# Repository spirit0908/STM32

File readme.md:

# Presentation of the project

## Modules
- Light management (dimmer, timer, LED strips...)
- Switch management
- Security Keypad
- Heat management

## Boards
- Development board (Proto board)
- Wall switch board
- Light control board
- Heater control board

## Architecture

Distributed network based on CAN bus

```
                        temp.                   wall
  I/O  I/O              sensor          light  switch
   |    |                 |               |       |
 +-+----+-----+     +-----+------+     +--+-------+-+
 |            |     |            |     |            |
 |  Module 1  |     |  Module 3  |     |  Moduel 5  |
 |            |     |            |     |            |
 +-----+------+     +-----+------+     +-----+------+ 
       |                  |                  |
       +-----+------------+-----+------------+-------- CAN Bus
             |                  |
       +-----+------+     +-----+------+ 
       |            |     |            |
       |  Module 2  |     |  Module 4  |
       |            |     |            |
       +-+-------+--+     +-----+------+
         |       |              |
       RFID   iButton      smart meter
      reader  reader        interface
```

## Boards

### Proto board
- LCD
- 4x switch
- 4x control output (RGBW)
- RS232
- CAN

### Relay board
- 4x switch
- 4x control output (RGBW)
- 6x relay output
- RS232
- CAN

### Intercom board
- 3x sensor input
- 2x relay output
- RS232
- CAN

# How to use

## How to compile

make

## How to execute the tests

make test

Test results location: out/tests/Test_report.html

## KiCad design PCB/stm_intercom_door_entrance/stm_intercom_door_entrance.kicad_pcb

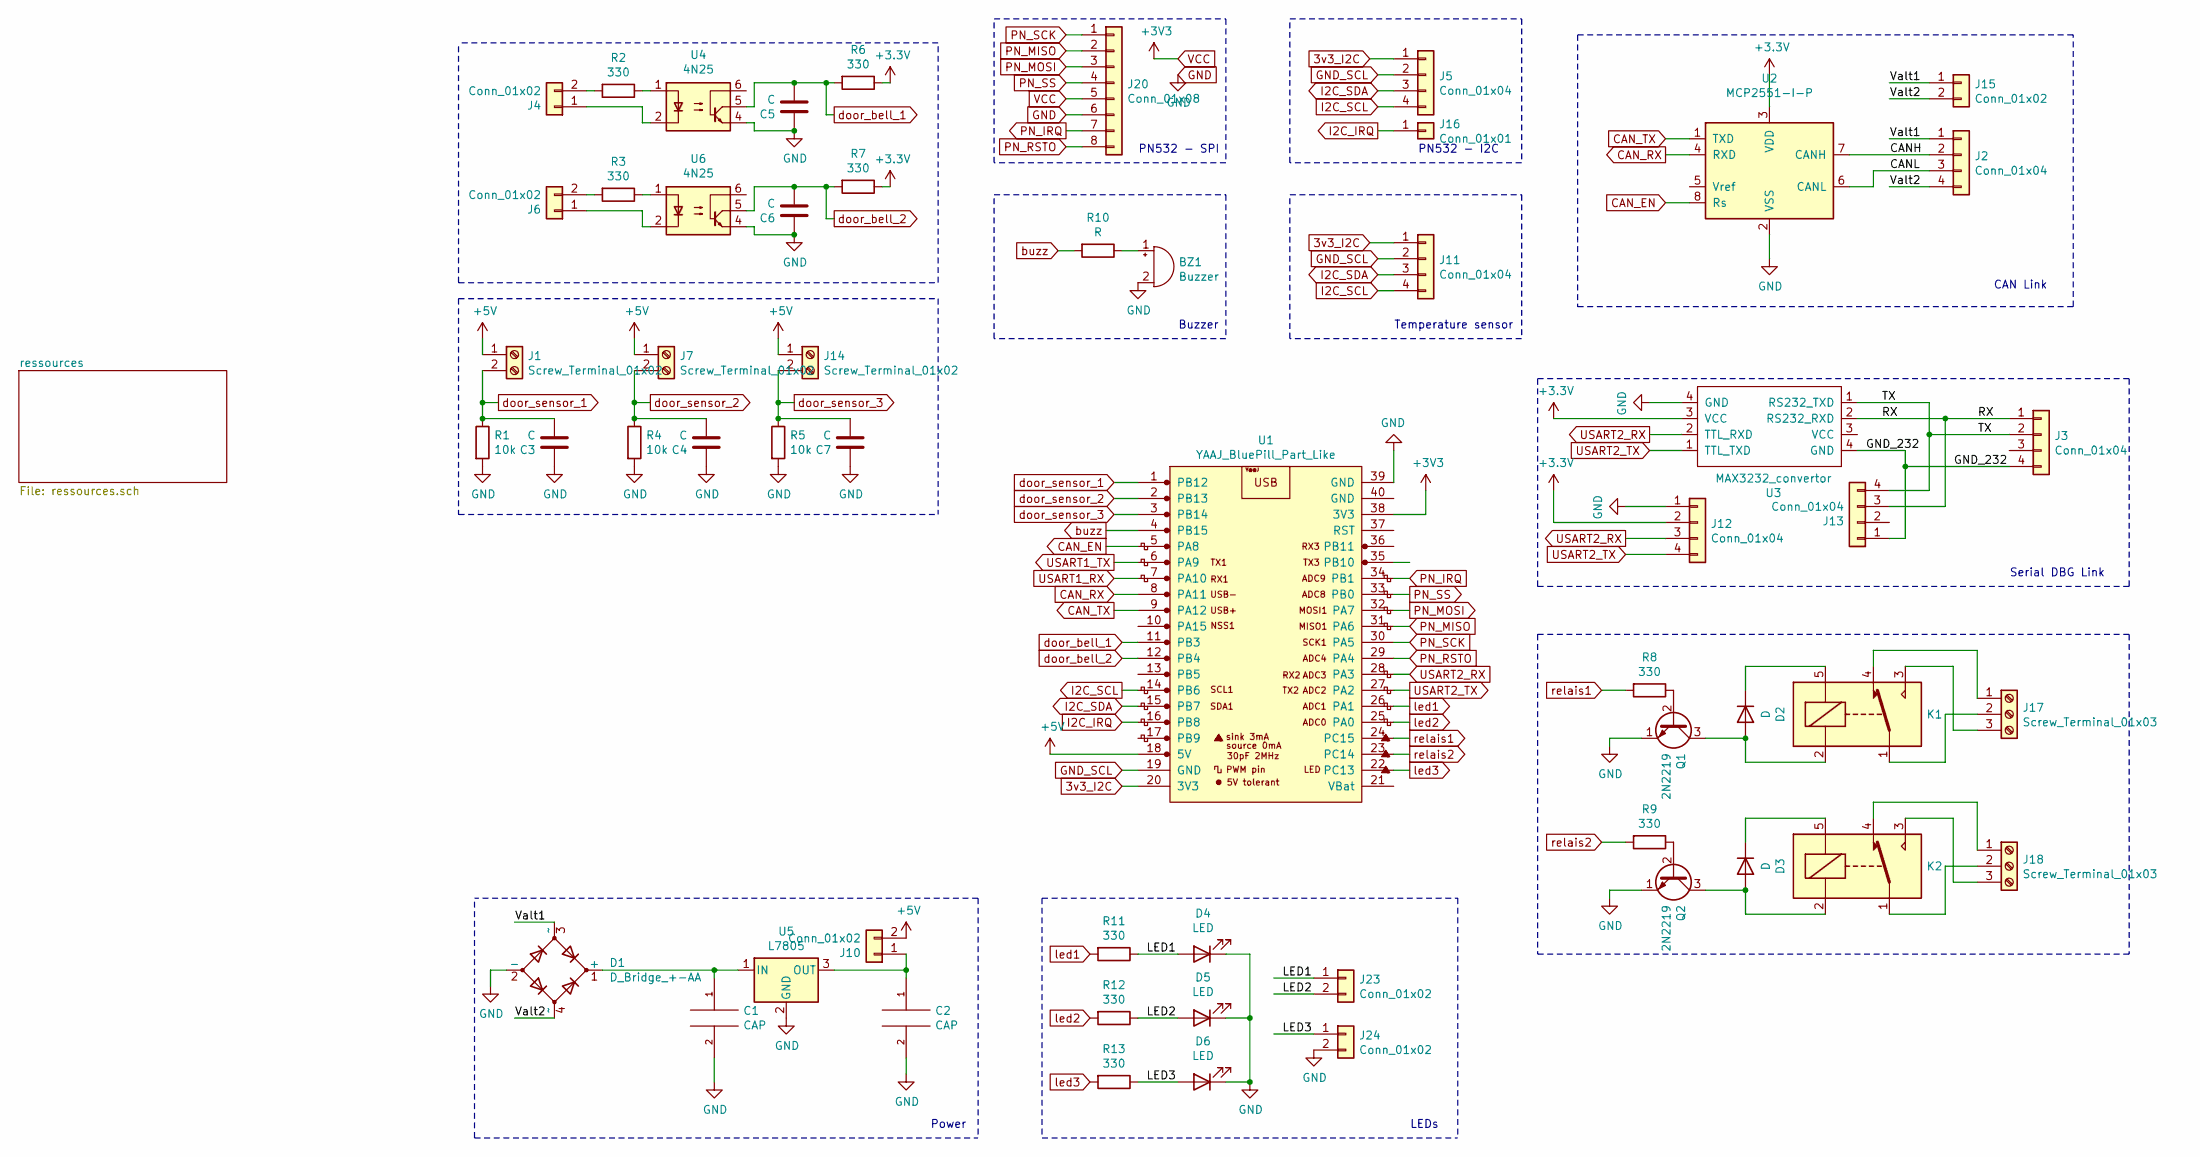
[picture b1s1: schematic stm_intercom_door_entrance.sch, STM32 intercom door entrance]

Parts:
BZ1: Buzzer; Buzzer_12x9.5RM7.6
C1: CAP; CP_Radial_D6.3mm_P2.50mm
C2: CAP; CP_Radial_D5.0mm_P2.50mm
C3, C4, C7: C; C_Disc_D4.3mm_W1.9mm_P5.00mm
C5, C6: C; CP_Radial_D5.0mm_P2.50mm
D1: D_Bridge_+-AA; Diode_Bridge_DIP-4_W7.62mm_P5.08mm
D2, D3: D; D_5W_P10.16mm_Horizontal
D4, D5, D6: LED
J1, J7, J14: Screw_Terminal_01x02; TerminalBlock_TE_282834-2_1x02_P2.54mm_Horizontal
J2: Conn_01x04; PinHeader_1x04_P2.54mm_Horizontal
J3, J5, J11, J12, J13: Conn_01x04; PinHeader_1x04_P2.54mm_Vertical
J4, J6, J10, J15, J23, J24: Conn_01x02; PinHeader_1x02_P2.54mm_Vertical
J16: Conn_01x01; PinHeader_1x01_P2.54mm_Vertical
J17, J18: Screw_Terminal_01x03; TerminalBlock_TE_282834-3_1x03_P2.54mm_Horizontal
J20: Conn_01x08; PinHeader_1x08_P2.54mm_Vertical
K1, K2: SANYOU_SRD_Form_C; Relay_SPDT_SANYOU_SRD_Series_Form_C
Q1, Q2: 2N2219; TO-39-3
R1, R4, R5: 10k; R_Axial_DIN0207_L6.3mm_D2.5mm_P10.16mm_Horizontal
R2, R3, R6, R7, R8, R9: 330; R_Axial_DIN0204_L3.6mm_D1.6mm_P7.62mm_Horizontal
R10: R; R_Axial_DIN0207_L6.3mm_D2.5mm_P10.16mm_Horizontal
R11, R12, R13: 330; R_Axial_DIN0204_L3.6mm_D1.6mm_P5.08mm_Vertical
U1: YAAJ_BluePill_Part_Like; YAAJ_BluePill_1
U2: MCP2551-I-P; DIP-8_W7.62mm
U3: MAX3232_convertor
U4, U6: 4N25; DIP-6_W7.62mm
U5: L7805; TO-220-3_Vertical

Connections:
3v3_I2C: J5.1, J11.1, U1.20 (3V3)
+5V: J1.1, J7.1, J10.2, J14.1, U1.18 (5V)
/CANH: J2.2, U2.7 (CANH)
/CANL: J2.3, U2.6 (CANL)
/GND_232: J3.4, J13.1, U3.4 (GND)
/LED1: D4.2 (A), J23.1, R11.1
/LED2: D5.2 (A), J23.2, R12.1
/LED3: D6.2 (A), J24.1, R13.1
/RX: J3.1, J13.3, U3.2 (RS232_RXD)
/TX: J3.2, J13.4, U3.1 (RS232_TXD)
/Valt1: D1.3 (~~), J2.1, J15.1
/Valt2: D1.4 (~~), J2.4, J15.2
CAN_EN: U1.5 (PA8), U2.8 (Rs)
CAN_RX: U1.8 (PA11), U2.4 (RXD)
CAN_TX: U1.9 (PA12), U2.1 (TXD)
GND: BZ1.2 (+), C1.2, C2.2, C3.1, C4.1, C5.1, C6.1, C7.1, D1.2 (-), D4.1 (K), D5.1 (K), D6.1 (K), J12.1, J20.6, J24.2, Q1.1 (E), Q2.1 (E), R1.2, R4.2, R5.2, U1.39 (GND), U2.2 (VSS), U3.4 (GND), U4.4, U5.2 (GND), U6.4; also elsewhere on the board
GND_SCL: J5.2, J11.2, U1.19 (GND)
I2C_IRQ: J16.1, U1.16 (PB8)
I2C_SCL: J5.4, J11.4, U1.14 (PB6)
I2C_SDA: J5.3, J11.3, U1.15 (PB7)
LED_iButton: U1.7 (PA10); also elsewhere on the board
unnamed: BZ1.1 (-), R10.1
unnamed: C1.1, D1.1 (+), U5.1 (IN)
unnamed: C2.1, J10.1, U5.3 (OUT)
unnamed: D2.1 (K), K1.5
unnamed: D2.2 (A), K1.2, Q1.3 (C)
unnamed: D3.1 (K), K2.5
unnamed: D3.2 (A), K2.2, Q2.3 (C)
unnamed: J4.1, U4.2
unnamed: J4.2, R2.2
unnamed: J6.1, U6.2
unnamed: J6.2, R3.2
unnamed: J17.1, K1.4
unnamed: J17.2, K1.1
unnamed: J17.3, K1.3
unnamed: J18.1, K2.4
unnamed: J18.2, K2.1
unnamed: J18.3, K2.3
unnamed: Q1.2 (B), R8.1
unnamed: Q2.2 (B), R9.1
unnamed: R2.1, U4.1
unnamed: R3.1, U6.1
PN_IRQ: J20.7, U1.34 (PB1)
PN_MISO: J20.2, U1.31 (PA6)
PN_MOSI: J20.3, U1.32 (PA7)
PN_RSTO: J20.8, U1.29 (PA4)
PN_SCK: J20.1, U1.30 (PA5)
PN_SS: J20.4, U1.33 (PB0)
USART2_RX: J12.3, U1.28 (PA3), U3.2 (RS232_RXD)
USART2_TX: J12.4, U1.27 (PA2), U3.1 (RS232_TXD)
buzz: R10.2, U1.4 (PB15)
door_bell_1: C5.2, R6.2, U1.11 (PB3), U4.5
door_bell_2: C6.2, R7.2, U1.12 (PB4), U6.5
door_sensor_1: C3.2, J1.2, R1.1, U1.1 (PB12)
door_sensor_2: C4.2, J7.2, R4.1, U1.2 (PB13)
door_sensor_3: C7.2, J14.2, R5.1, U1.3 (PB14)
iButton_Data: U1.6 (PA9); also elsewhere on the board
led1: R11.2, U1.26 (PA1)
led2: R12.2, U1.25 (PA0)
led3: R13.2, U1.22 (PC13)
relais1: R8.2, U1.24 (PC15)
relais2: R9.2, U1.23 (PC14)

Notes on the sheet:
Serial DBG Link
CAN Link
PN532 - I2C
Temperature sensor
Power
PN532 - SPI
Buzzer
LEDs

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
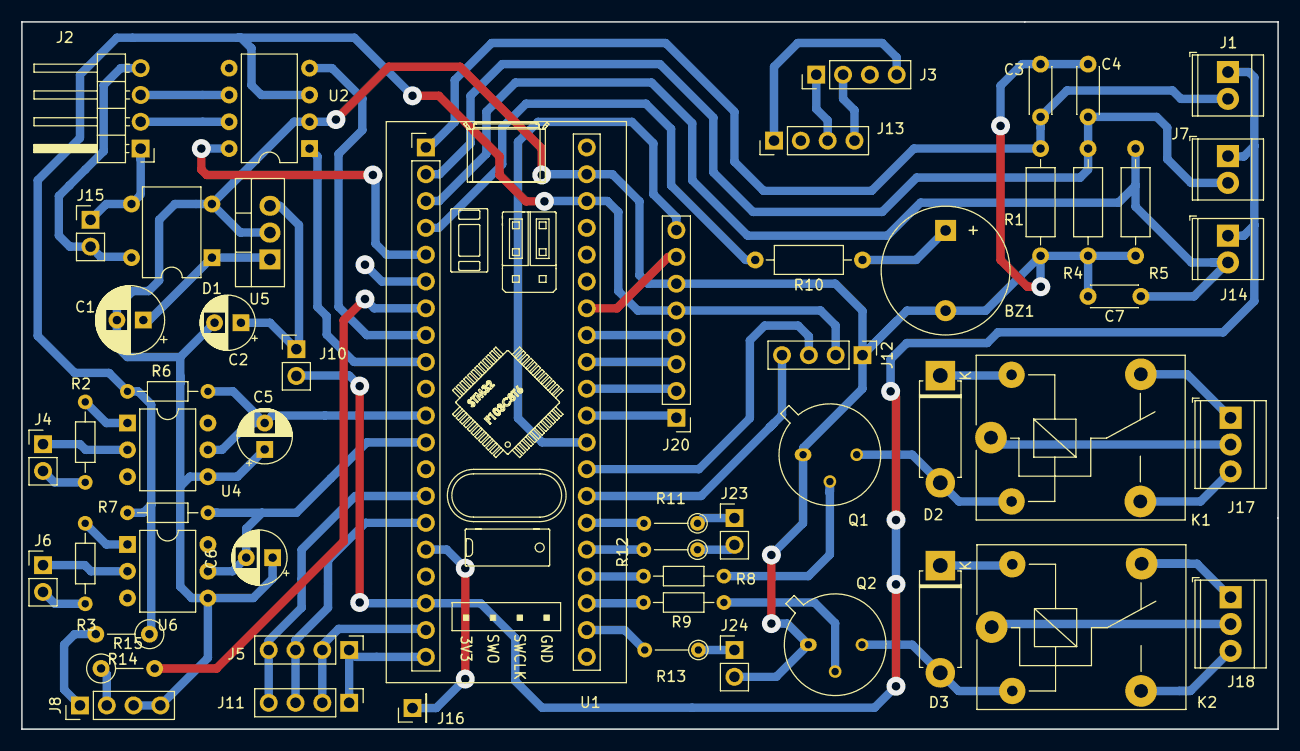
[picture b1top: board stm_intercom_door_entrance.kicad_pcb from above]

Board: 2 copper layers, 119.0 x 67.0 mm, 55 parts (0 on the bottom side), 64 nets.

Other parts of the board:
J8: Conn_01x04; PinHeader_1x04_P2.54mm_Vertical
R14, R15: 10k; R_Axial_DIN0207_L6.3mm_D2.5mm_P5.08mm_Vertical

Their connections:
GND: J8.3, J8.4; also elsewhere on the board
LED_iButton: R15.2; also elsewhere on the board
unnamed: J8.2, R15.1
iButton_Data: J8.1, R14.2; also elsewhere on the board

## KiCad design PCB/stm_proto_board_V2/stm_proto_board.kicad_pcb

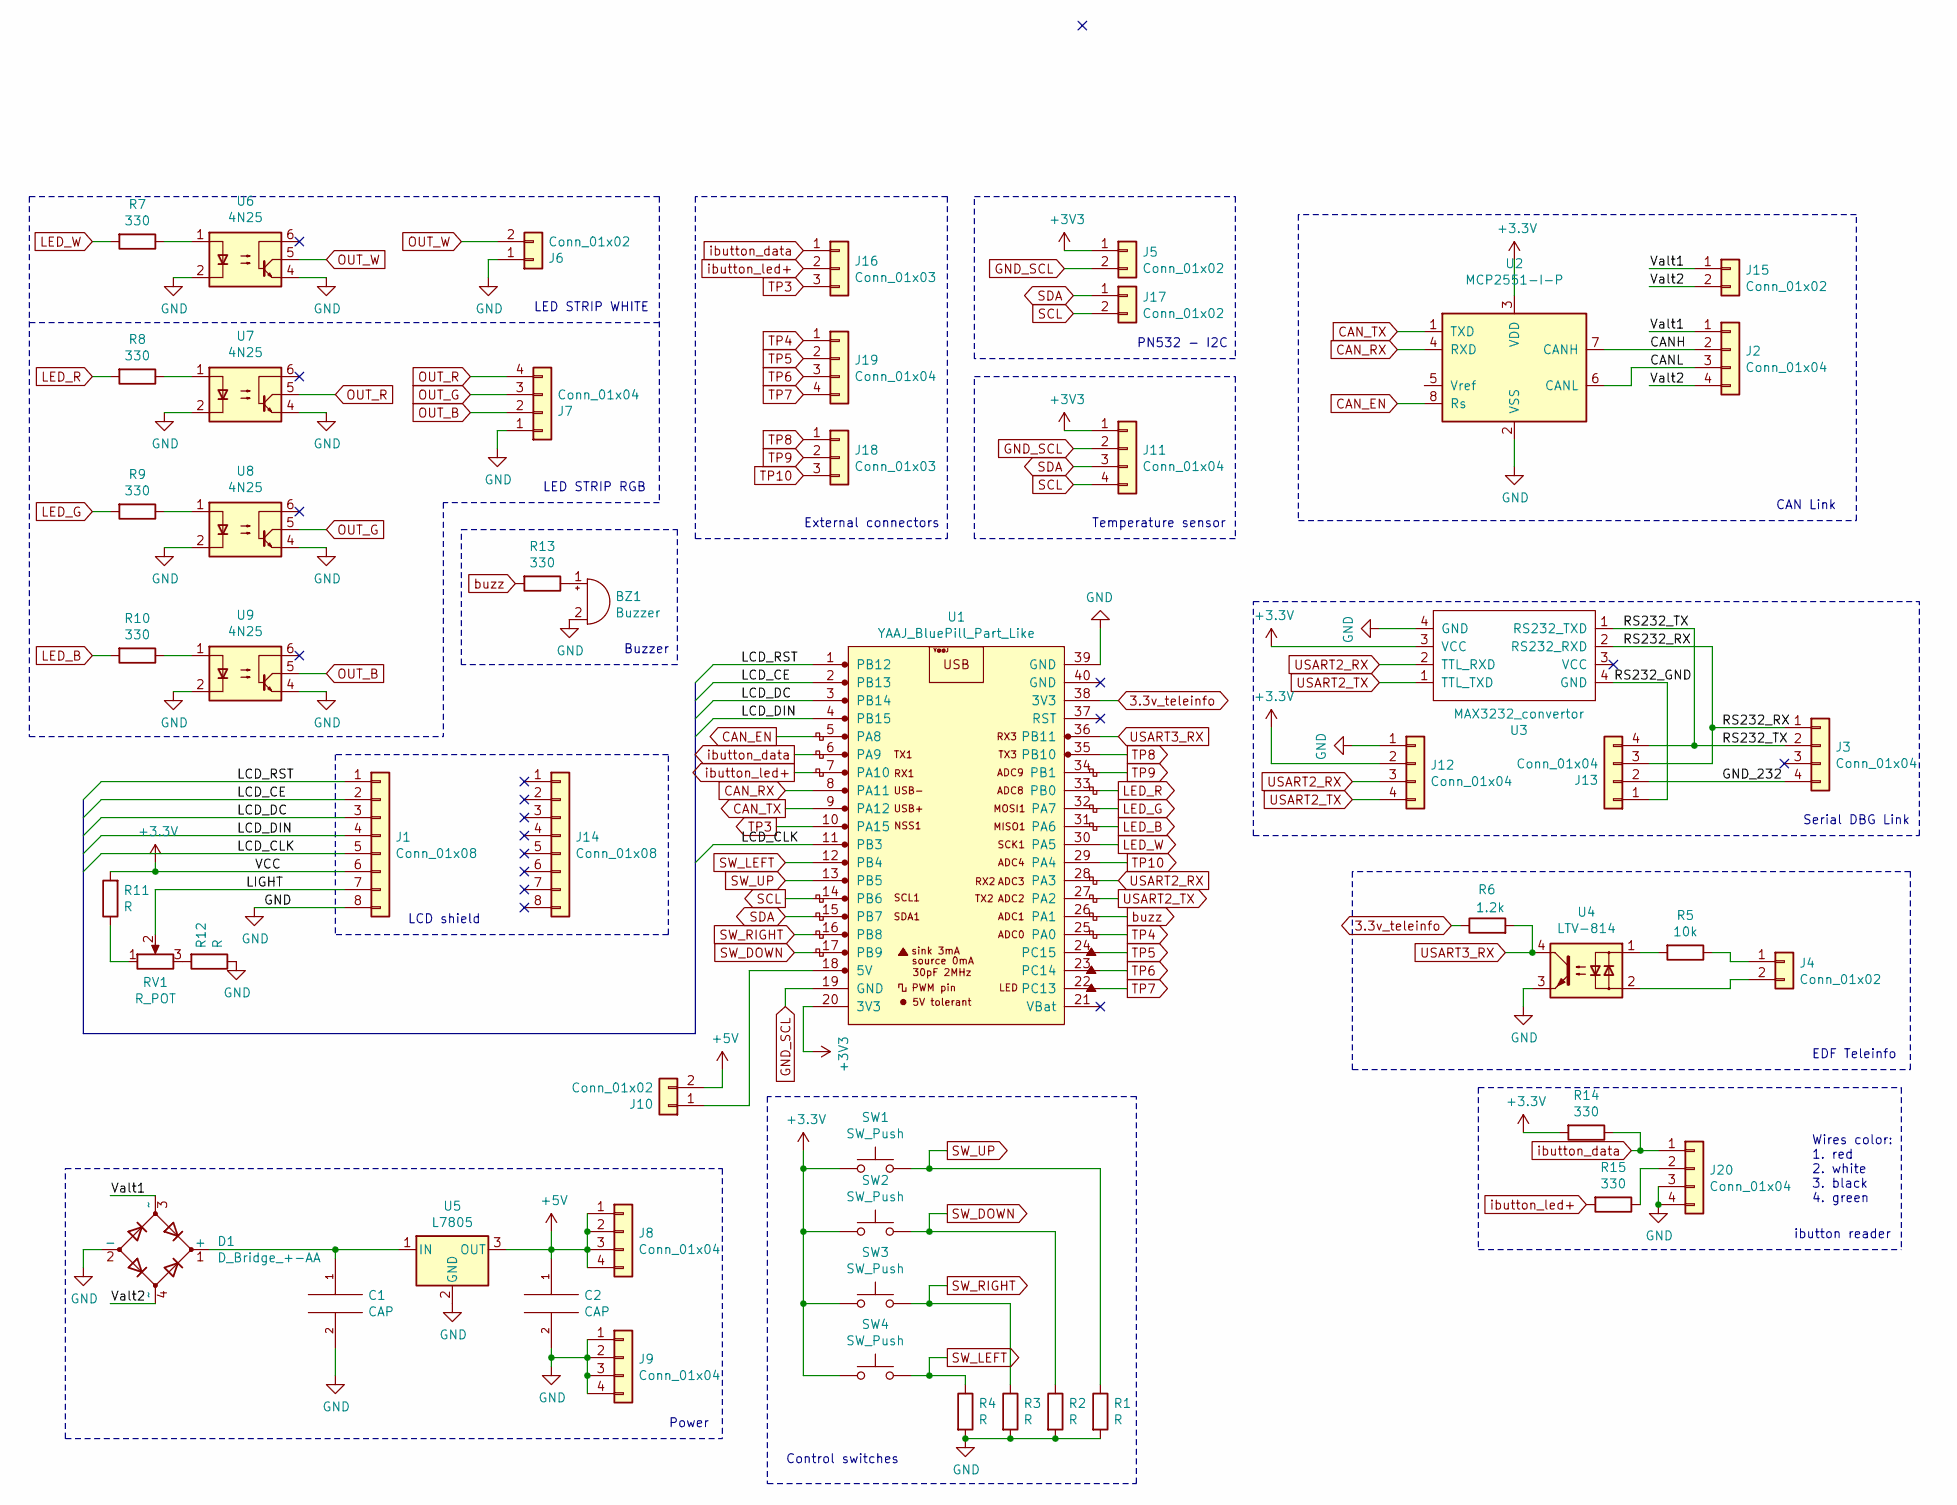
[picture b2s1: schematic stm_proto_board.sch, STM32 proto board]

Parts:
BZ1: Buzzer; Buzzer_12x9.5RM7.6
C1: CAP; CP_Radial_D6.3mm_P2.50mm
C2: CAP; CP_Radial_D5.0mm_P2.50mm
D1: D_Bridge_+-AA; Diode_Bridge_DIP-4_W7.62mm_P5.08mm
J1, J14: Conn_01x08; PinHeader_1x08_P2.54mm_Vertical
J2: Conn_01x04; PinHeader_1x04_P2.54mm_Horizontal
J3, J7, J8, J9, J11, J12, J13, J19, J20: Conn_01x04; PinHeader_1x04_P2.54mm_Vertical
J4, J5, J6, J10, J15, J17: Conn_01x02; PinHeader_1x02_P2.54mm_Vertical
J16, J18: Conn_01x03; PinHeader_1x03_P2.54mm_Vertical
R1, R2, R3: R; R_Axial_DIN0207_L6.3mm_D2.5mm_P15.24mm_Horizontal
R4, R11, R12: R; R_Axial_DIN0207_L6.3mm_D2.5mm_P10.16mm_Horizontal
R5: 10k; R_Axial_DIN0204_L3.6mm_D1.6mm_P5.08mm_Horizontal
R6: 1.2k; R_Axial_DIN0204_L3.6mm_D1.6mm_P7.62mm_Horizontal
R7, R8, R9, R10, R13, R14, R15: 330; R_Axial_DIN0204_L3.6mm_D1.6mm_P7.62mm_Horizontal
RV1: R_POT; Potentiometer_Bourns_3266Z_Horizontal
SW1, SW2, SW3, SW4: SW_Push; SW_PUSH_6mm
U1: YAAJ_BluePill_Part_Like; YAAJ_BluePill_1
U2: MCP2551-I-P; DIP-8_W7.62mm
U3: MAX3232_convertor
U4: LTV-814; DIP-4_W7.62mm
U5: L7805; TO-220-3_Horizontal_TabUp
U6, U7, U8, U9: 4N25; DIP-6_W7.62mm

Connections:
3.3v_teleinfo: R6.1, U1.38 (3V3)
+5V: C2.1, J8.1, J8.2, J8.3, J8.4, J10.2, U5.3 (OUT)
/CANH: J2.2, U2.7 (CANH)
/CANL: J2.3, U2.6 (CANL)
/GND_232: J3.4, J13.2
/LCD_CE: J1.2, U1.2 (PB13)
/LCD_CLK: J1.5, U1.11 (PB3)
/LCD_DC: J1.3, U1.3 (PB14)
/LCD_DIN: J1.4, U1.4 (PB15)
/LCD_RST: J1.1, U1.1 (PB12)
/LIGHT: J1.7, RV1.2
/RS232_GND: J13.1, U3.4 (GND)
/RS232_RX: J3.1, J13.3, U3.2 (RS232_RXD)
/RS232_TX: J3.2, J13.4, U3.1 (RS232_TXD)
/Valt1: D1.3 (~~), J2.1, J15.1
/Valt2: D1.4 (~~), J2.4, J15.2
CAN_EN: U1.5 (PA8), U2.8 (Rs)
CAN_RX: U1.8 (PA11), U2.4 (RXD)
CAN_TX: U1.9 (PA12), U2.1 (TXD)
GND: BZ1.2 (+), C1.2, C2.2, D1.2 (-), J1.8, J6.1, J7.1, J9.1, J9.2, J9.3, J9.4, J12.1, J20.3, J20.4, R1.2, R2.2, R3.2, R4.2, R12.1, U1.39 (GND), U2.2 (VSS), U3.4 (GND), U4.3, U5.2 (GND), U6.2, U6.4, U7.2, U7.4, U8.2, U8.4, U9.2, U9.4
GND_SCL: J5.2, J11.2, U1.19 (GND)
LED_B: R10.2, U1.31 (PA6)
LED_G: R9.2, U1.32 (PA7)
LED_R: R8.2, U1.33 (PB0)
LED_W: R7.2, U1.30 (PA5)
unnamed: BZ1.1 (-), R13.1
unnamed: C1.1, D1.1 (+), U5.1 (IN)
unnamed: J4.1, R5.1
unnamed: J4.2, U4.2
unnamed: J10.1, U1.18 (5V)
unnamed: J20.2, R15.1
unnamed: R5.2, U4.1
unnamed: R7.1, U6.1
unnamed: R8.1, U7.1
unnamed: R9.1, U8.1
unnamed: R10.1, U9.1
unnamed: R11.1, RV1.1
unnamed: R12.2, RV1.3
OUT_B: J7.2, U9.5
OUT_G: J7.3, U8.5
OUT_R: J7.4, U7.5
OUT_W: J6.2, U6.5
SCL: J11.4, J17.2, U1.14 (PB6)
SDA: J11.3, J17.1, U1.15 (PB7)
SW_DOWN: R2.1, SW2.2, U1.17 (PB9)
SW_LEFT: R4.1, SW4.2, U1.12 (PB4)
SW_RIGHT: R3.1, SW3.2, U1.16 (PB8)
SW_UP: R1.1, SW1.2, U1.13 (PB5)
TP3: J16.3, U1.10 (PA15)
TP4: J19.1, U1.25 (PA0)
TP5: J19.2, U1.24 (PC15)
TP6: J19.3, U1.23 (PC14)
TP7: J19.4, U1.22 (PC13)
TP8: J18.1, U1.35 (PB10)
TP9: J18.2, U1.34 (PB1)
TP10: J18.3, U1.29 (PA4)
USART2_RX: J12.3, U1.28 (PA3), U3.2 (RS232_RXD)
USART2_TX: J12.4, U1.27 (PA2), U3.1 (RS232_TXD)
USART3_RX: R6.2, U1.36 (PB11), U4.4
buzz: R13.2, U1.26 (PA1)
ibutton_data: J16.1, J20.1, R14.1, U1.6 (PA9)
ibutton_led+: J16.2, R15.2, U1.7 (PA10)

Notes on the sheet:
Serial DBG Link
EDF Teleinfo
CAN Link
LCD shield
PN532 - I2C
LED STRIP WHITE
Power
Control switches
Buzzer
External connectors
Temperature sensor
LED STRIP RGB
ibutton reader
Wires color: 1. red 2. white 3. black 4. green

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
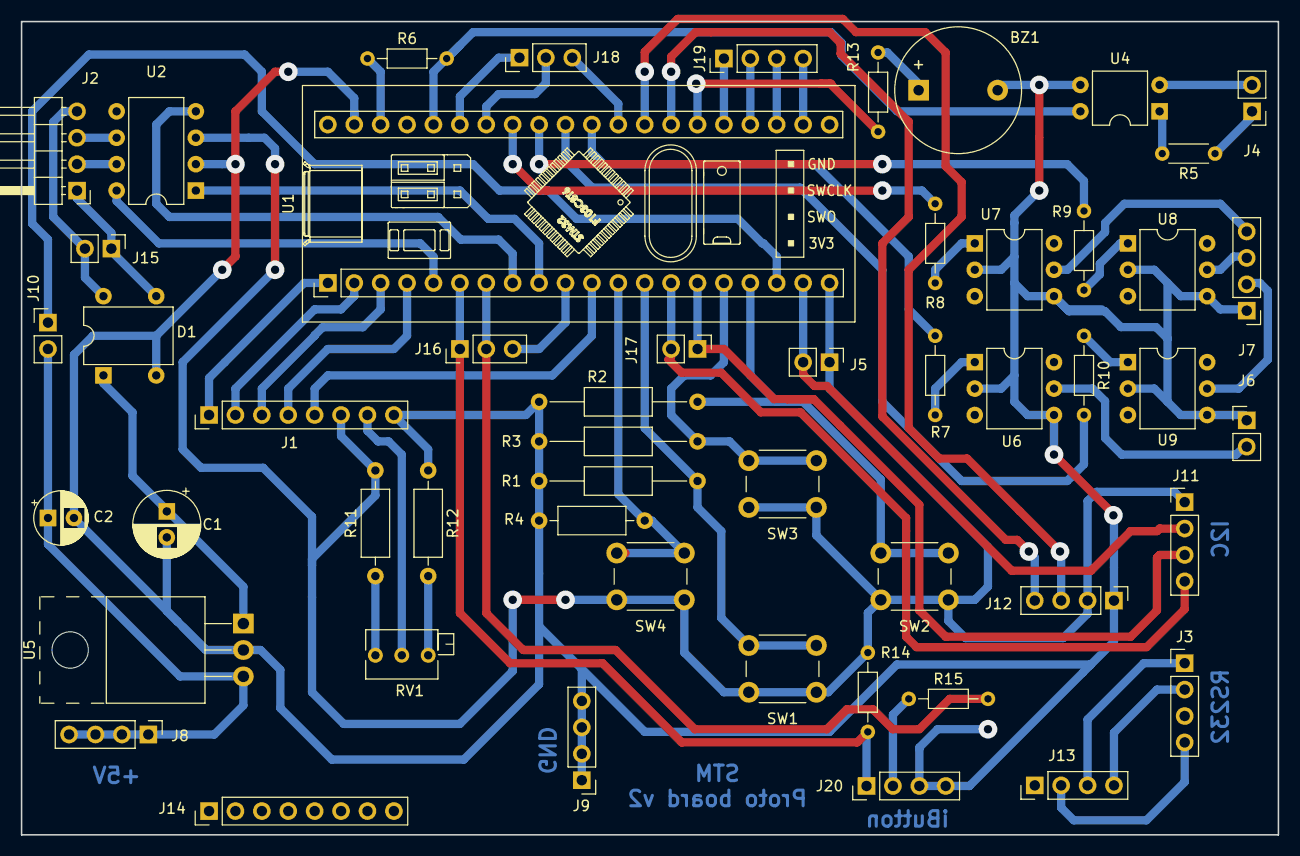
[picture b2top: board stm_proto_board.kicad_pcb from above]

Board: 2 copper layers, 120.9 x 78.2 mm, 52 parts (0 on the bottom side), 62 nets.

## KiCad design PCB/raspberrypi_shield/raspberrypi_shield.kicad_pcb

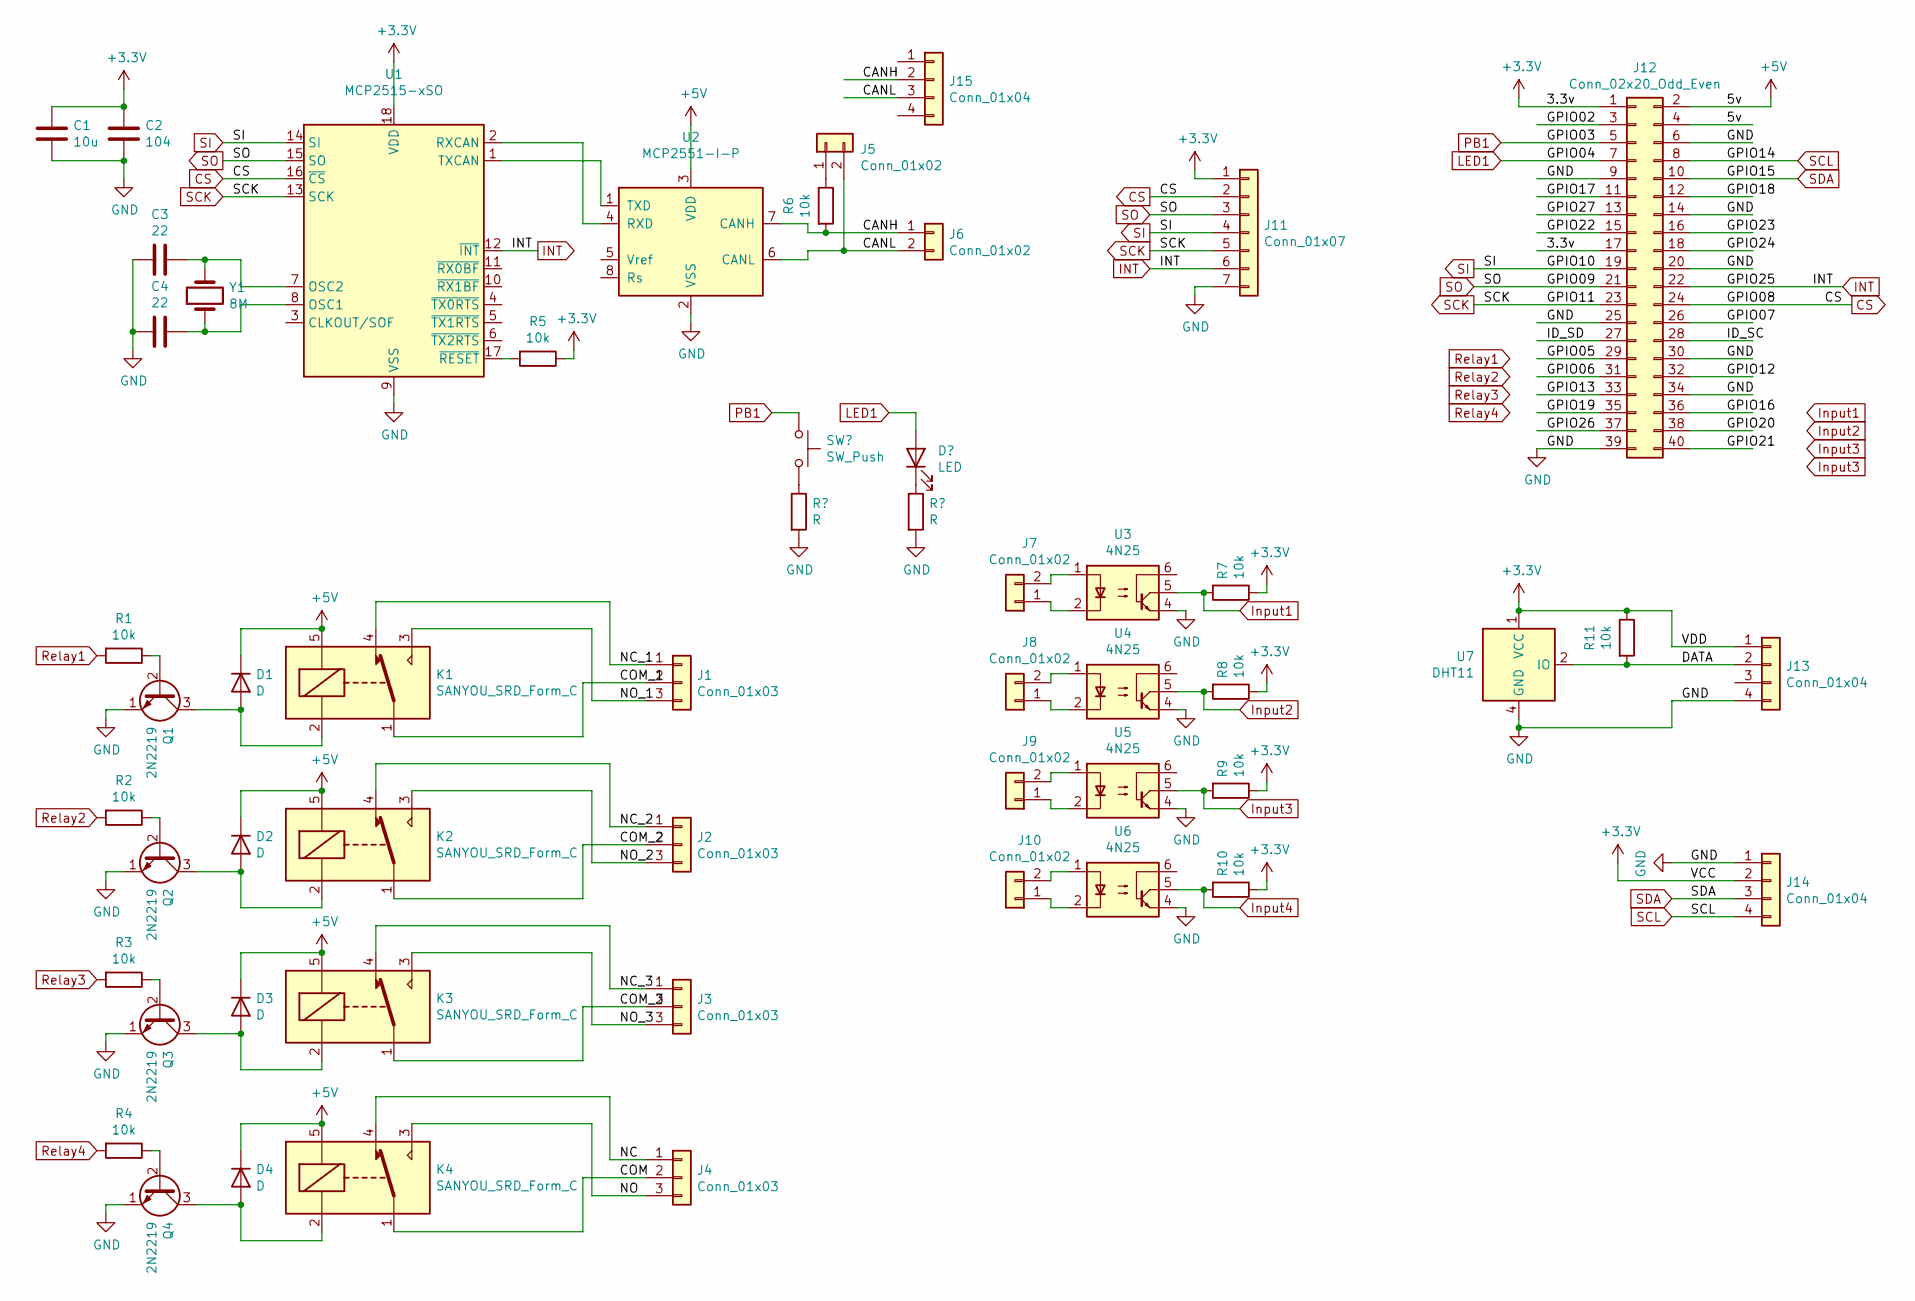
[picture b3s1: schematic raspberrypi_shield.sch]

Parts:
C1: 10u; C_Disc_D3.0mm_W1.6mm_P2.50mm
C2: 104; C_Disc_D3.0mm_W1.6mm_P2.50mm
C3, C4: 22; C_Disc_D3.0mm_W1.6mm_P2.50mm
D1, D2, D3, D4: D; D_A-405_P7.62mm_Horizontal
J1, J2, J3, J4: Conn_01x03; PinHeader_1x03_P2.54mm_Vertical
J5, J6, J7, J8, J9, J10: Conn_01x02; PinHeader_1x02_P2.54mm_Vertical
J11: Conn_01x07; PinHeader_1x07_P2.54mm_Vertical
J12: Conn_02x20_Odd_Even; PinHeader_2x20_P2.54mm_Vertical
J13, J14, J15: Conn_01x04; PinHeader_1x04_P2.54mm_Vertical
K1, K2, K3, K4: SANYOU_SRD_Form_C; Relay_SPDT_SANYOU_SRD_Series_Form_C
Q1, Q2, Q3, Q4: 2N2219; TO-39-3
R1, R2, R3, R4, R5, R6, R7, R8, R9, R10, R11: 10k; R_Axial_DIN0204_L3.6mm_D1.6mm_P5.08mm_Horizontal
U1: MCP2515-xSO; SOIC-18W_7.5x11.6mm_P1.27mm
U2: MCP2551-I-P; HTSOP-8-1EP_3.9x4.9mm_P1.27mm_EP2.4x3.2mm_ThermalVias
U3, U4, U5, U6: 4N25; DIP-6_W7.62mm
U7: DHT11; Aosong_DHT11_5.5x12.0_P2.54mm
Y1: 8M; R_Axial_DIN0411_L9.9mm_D3.6mm_P7.62mm_Vertical

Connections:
+3V3: C1.2, C2.2, J11.1, J12.1, J12.17, J13.1, J14.2, R5.1, R7.1, R8.1, R9.1, R10.1, R11.1, U1.18 (VDD), U7.1 (VCC)
+5V: D1.1 (K), D2.1 (K), D3.1 (K), D4.1 (K), J12.2, J12.4, K1.5, K2.5, K3.5, K4.5, U2.3 (VDD)
/CANH: J6.1, J15.2, R6.2, U2.7 (CANH)
/CANL: J5.2, J6.2, J15.3, U2.6 (CANL)
/COM: J4.2, K4.1
/COM_1: J1.2, K1.1
/COM_2: J2.2, K2.1
/COM_3: J3.2, K3.1
/DATA: J13.2, R11.2, U7.2 (IO)
/GPIO02: J12.3
/GPIO03: J12.5
/GPIO04: J12.7
/GPIO05: J12.29
/GPIO06: J12.31
/GPIO07: J12.26
/GPIO12: J12.32
/GPIO13: J12.33
/GPIO16: J12.36
/GPIO17: J12.11
/GPIO18: J12.12
/GPIO19: J12.35
/GPIO20: J12.38
/GPIO21: J12.40
/GPIO22: J12.15
/GPIO23: J12.16
/GPIO24: J12.18
/GPIO26: J12.37
/GPIO27: J12.13
/ID_SC: J12.28
/ID_SD: J12.27
/NC: J4.1, K4.4
/NC_1: J1.1, K1.4
/NC_2: J2.1, K2.4
/NC_3: J3.1, K3.4
/NO: J4.3, K4.3
/NO_1: J1.3, K1.3
/NO_2: J2.3, K2.3
/NO_3: J3.3, K3.3
CS: J11.2, J12.24, U1.16 (~CS)
GND: C1.1, C2.1, C3.1, C4.1, J11.7, J12.6, J12.9, J12.14, J12.20, J12.25, J12.30, J12.34, J12.39, J13.4, J14.1, Q1.1 (E), Q2.1 (E), Q3.1 (E), Q4.1 (E), U1.9 (VSS), U2.2 (VSS), U3.4, U4.4, U5.4, U6.4, U7.4 (GND)
INT: J11.6, J12.22, U1.12 (~INT)
Input1: R7.2, U3.5
Input2: R8.2, U4.5
Input3: R9.2, U5.5
Input4: R10.2, U6.5
unnamed: C3.2, U1.7 (OSC2), Y1.2
unnamed: C4.2, U1.8 (OSC1), Y1.1
unnamed: D1.2 (A), K1.2, Q1.3 (C)
unnamed: D2.2 (A), K2.2, Q2.3 (C)
unnamed: D3.2 (A), K3.2, Q3.3 (C)
unnamed: D4.2 (A), K4.2, Q4.3 (C)
unnamed: J5.1, R6.1
unnamed: J7.1, U3.2
unnamed: J7.2, U3.1
unnamed: J8.1, U4.2
unnamed: J8.2, U4.1
unnamed: J9.1, U5.2
unnamed: J9.2, U5.1
unnamed: J10.1, U6.2
unnamed: J10.2, U6.1
unnamed: Q1.2 (B), R1.1
unnamed: Q2.2 (B), R2.1
unnamed: Q3.2 (B), R3.1
unnamed: Q4.2 (B), R4.1
unnamed: R5.2, U1.17 (~RESET)
unnamed: U1.1 (TXCAN), U2.1 (TXD)
unnamed: U1.2 (RXCAN), U2.4 (RXD)
SCK: J11.5, J12.23, U1.13 (SCK)
SCL: J12.8, J14.4
SDA: J12.10, J14.3
SI: J11.4, J12.19, U1.14 (SI)
SO: J11.3, J12.21, U1.15 (SO)

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
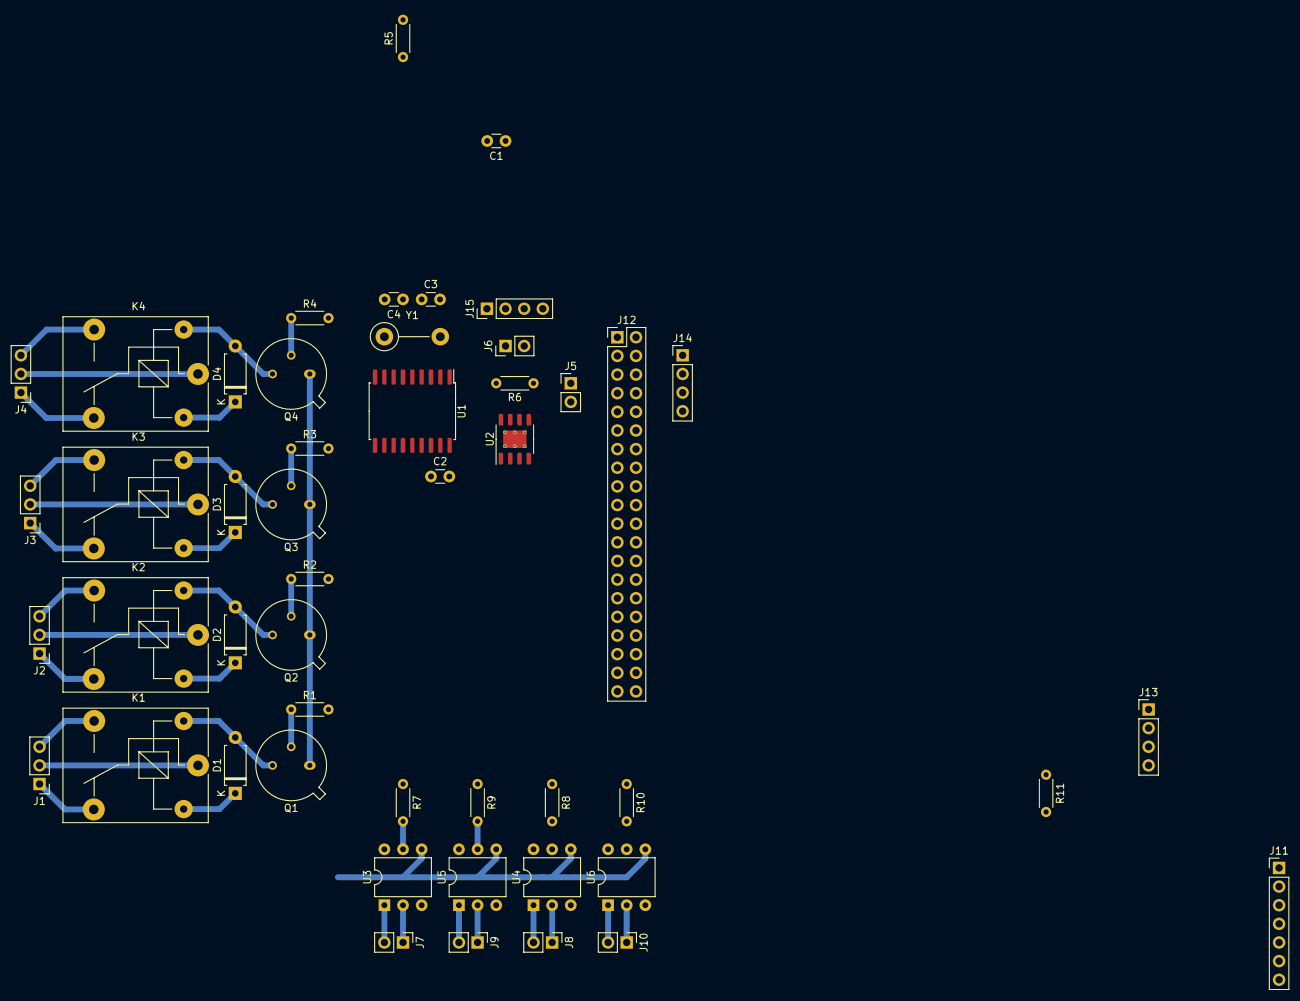
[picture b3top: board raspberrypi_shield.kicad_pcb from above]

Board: 2 copper layers, 49 parts (0 on the bottom side), 52 nets.

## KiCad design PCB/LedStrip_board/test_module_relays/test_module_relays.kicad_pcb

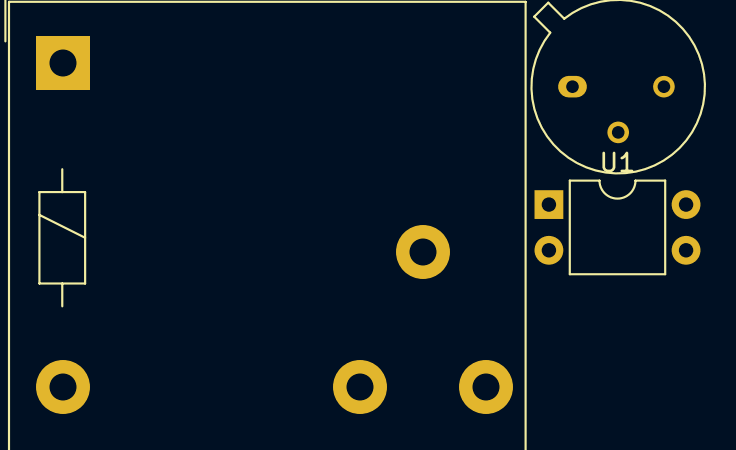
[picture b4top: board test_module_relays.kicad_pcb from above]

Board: 2 copper layers, 3 parts (0 on the bottom side), 3 nets, no tracks yet.

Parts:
K1: FINDER-40.11; Relay_SPDT_Finder_40.11
Q1: BC141; TO-39-3
U1: PC817; DIP-4_W7.62mm

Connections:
+5V: K1.A1, U1.4
GND: Q1.1, U1.2
unnamed: K1.A2, Q1.3

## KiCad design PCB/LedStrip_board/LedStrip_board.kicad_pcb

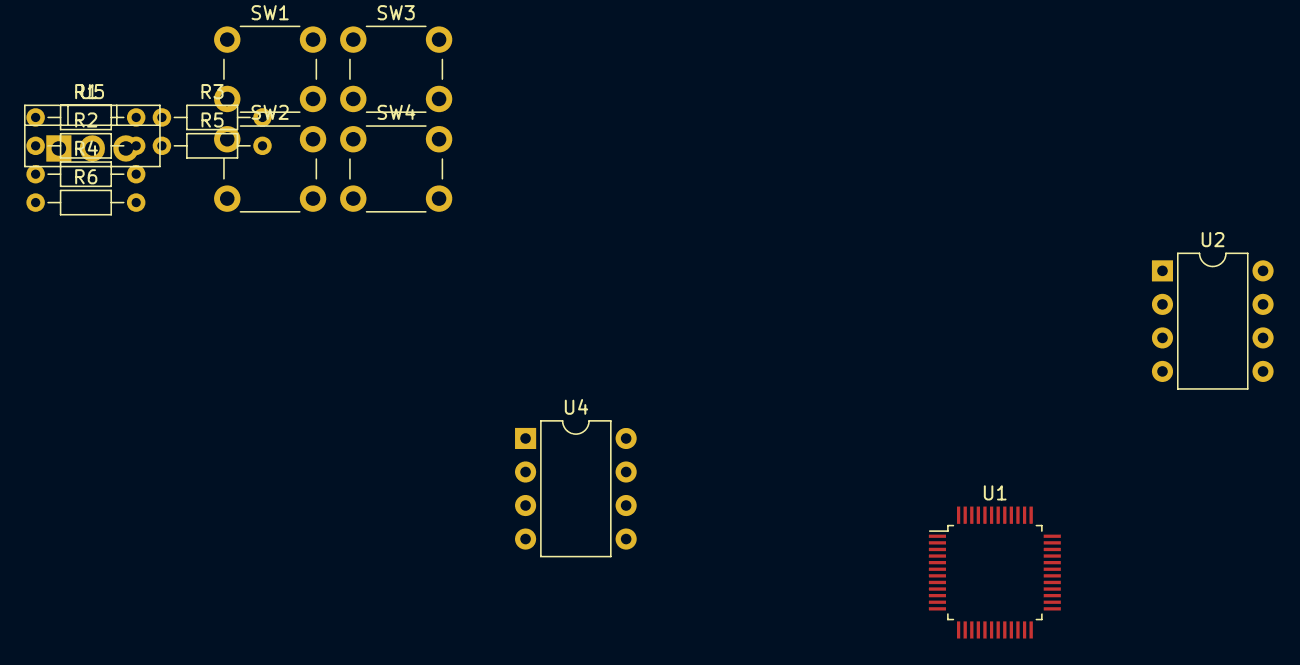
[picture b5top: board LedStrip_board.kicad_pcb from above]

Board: 2 copper layers, 14 parts (0 on the bottom side), 12 nets, no tracks yet.

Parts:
R1, R2, R3, R4: R; R_Axial_DIN0204_L3.6mm_D1.6mm_P7.62mm_Horizontal
R5: 10k; R_Axial_DIN0204_L3.6mm_D1.6mm_P7.62mm_Horizontal
R6: 1.2k; R_Axial_DIN0204_L3.6mm_D1.6mm_P7.62mm_Horizontal
SW1, SW2, SW3, SW4: SW_Push; SW_PUSH_6mm
U1: STM32F103C8T6_shield; LQFP-48_7x7mm_P0.5mm
U2: MCP2551-I-P; DIP-8_W7.62mm
U4: LTV-814; DIP-8_W7.62mm
U5: L7805; TO-220-3_Vertical

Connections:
+3V3: R6.1, SW1.1, SW2.1, SW3.1, SW4.1, U1.3, U2.3
+5V: U1.23, U5.3
CAN_EN: U1.28, U2.8
CAN_RX: U1.33, U2.4
CAN_TX: U1.32, U2.1
GND: R1.2, R2.2, R3.2, R4.2, U1.22, U2.2, U4.3
unnamed: R5.2, U4.1
SW_DOWN: R2.1, SW2.2, U1.18
SW_LEFT: R4.1, SW4.2, U1.16
SW_RIGHT: R3.1, SW3.2, U1.17
SW_UP: R1.1, SW1.2, U1.19
USART3_RX: R6.2, U1.5, U4.4

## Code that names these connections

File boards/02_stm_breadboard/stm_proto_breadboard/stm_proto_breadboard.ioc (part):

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PB13.GPIOParameters=PinState,GPIO_Label
PD1-OSC_OUT.Mode=HSE-External-Oscillator
PA10.Mode=Asynchronous
Mcu.UserName=STM32F103C8Tx
PA10.GPIO_PuPd=GPIO_PULLUP
PB14.GPIO_Label=RELAY3
PA11.Mode=CAN_Activate
PD0-OSC_IN.Signal=RCC_OSC_IN
PB13.GPIO_Label=RELAY2
PB13.Signal=GPIO_Output
PB15.Signal=GPIO_Output
RCC.SYSCLKSource=RCC_SYSCLKSOURCE_PLLCLK
PD1-OSC_OUT.Signal=RCC_OSC_OUT
PA13.Signal=SYS_JTMS-SWDIO
PA3.Mode=Asynchronous
PA9.Mode=Asynchronous
PA12.Signal=CAN_TX
PA9.Signal=USART1_TX
PD0-OSC_IN.Mode=HSE-External-Oscillator
PB14.Signal=GPIO_Output
board=custom
PB12.GPIO_Label=RELAY1
PB13.PinState=GPIO_PIN_RESET
PB15.GPIO_Label=RELAY4
PA14.Mode=Serial_Wire
PA10.GPIOParameters=GPIO_PuPd
PB15.GPIOParameters=GPIO_Label
PA13.Mode=Serial_Wire
Mcu.Name=STM32F103C(8-B)Tx
PA2.Signal=USART2_TX
RCC.SYSCLKFreq_VALUE=72000000
Mcu.Package=LQFP48
PA12.Mode=CAN_Activate
PA11.Signal=CAN_RX
PA14.Signal=SYS_JTCK-SWCLK
PA10.Signal=USART1_RX
PB14.GPIOParameters=GPIO_Label
PA2.Mode=Asynchronous
PB12.GPIOParameters=GPIO_Label
PB12.Signal=GPIO_Output
PA3.Signal=USART2_RX

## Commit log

2018-03-11 implement USART module
2018-03-11 Change path of compiled files: .o in obj/ and .bin, .elf and .map in out/ folders
2018-03-28 separate files in folders obj/ and out/
2018-04-02 Add Teleinfo module
2018-04-09 Implement CAN bus module
2018-04-13 Add scheduler and Fifo management
2018-08-11 add missing ld file
2018-08-11 Create schematic + add debug command in makefile
2018-08-12 Add PWM + template code for other modules
2018-08-12 Add board photos
2018-08-12 prototype photos
2018-08-31 Add Lcd menu
2018-09-03 Add 3 PWM channels
2018-09-09 clean up
2018-09-13 Add PushButton module
2018-10-28 Add LED strip management
2019-02-09 LedStrip management
2019-02-10 serial debug
2019-10-25 Update module Teleinfo + create test file
2020-02-15 revert stm32f10x_it.c
2020-02-23 Add Heating module + cleanup
2020-02-29 move tests Fifo module
2020-02-29 Add pinCode module
2020-02-29 update code and description
2020-02-29 current verson of schematic
2020-02-29 Format files with source/header template
2020-02-29 Add enc28j60 on schematic + convert pinout in md format
2020-03-01 update pinCode module
2020-03-01 create xml file to describe the microcontroler pins
2020-03-01 Reorder initializations in main function + improve pinout sheet
2020-03-01 implement xsl table generator
2020-04-15 update xml xsl
2020-06-01 Rework Teleinfo module
2020-06-10 fix warnings and code
2020-07-25 test
2020-07-25 revert
2020-09-26 Add module configurator
2020-09-26 add folder out
2020-09-26 Update makefile for github actions remove out folder and create it from makefile
2020-09-26 Add module Security
2020-10-16 Create module Heating
2020-10-16 update tests for module Heating
2020-10-16 update test + correct code
2020-10-18 Update PCB proto-board
2020-10-20 PCB design
2020-10-21 update PCB
2020-10-21 Cleanup backup files
2020-10-22 update module configuration generator
2020-10-24 Improve tests and generate result report
2020-10-25 Generate test report
2020-10-25 add PCB proto board wrapped + raspberry + cables
2020-10-25 github workflow - Add test step
2020-10-25 Update test teleinfo
2020-10-25 add test report generator to teleinfo
2020-10-25 add test scripts
2020-10-26 test returns the number of failures
2020-11-07 Update schematic SDA/SDL pins
2020-11-07 Add intercom/door board
2020-11-07 rename
2020-11-07 Update schematic
2020-11-08 update schematics
2020-11-11 Update test report generation
2020-11-11 update boards descriptions
2020-12-13 Clean up + improve pin module
2020-12-13 fix build
2020-12-22 Update PCB proto board
2020-12-22 PCB update
2020-12-22 change folders structure
2020-12-22 rename board 01
2021-02-14 Restructure modules
2021-02-14 make from build folder
2021-02-14 update tests generation
2021-02-14 Update makefiles for test execution
2021-02-14 Add root makefile
2021-02-26 Update Light module
2021-02-26 Add proto breadboard configured zith STM32CubeIde
2021-02-26 update templates
2021-02-26 Add test common
2021-04-02 Update micro 3
2021-04-02 separate board config from code ressources
2021-04-02 Add PCB for module 3
2021-06-02 Move current code to subfolder
2021-06-02 Add new project from STM32CubeIde
2022-03-31 Add pn532 library
